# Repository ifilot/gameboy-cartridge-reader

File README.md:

# Gameboy Cartridge Reader

This project is a Gameboy cartridge reader designed around the Atmel ATmega32u4
microcontroller. It provides an easy way to interface with Gameboy cartridges,
enabling data reading, writing, and backup. The design includes a custom PCB,
firmware for the 32u4, and a simple GUI for user interaction.

> [!NOTE]
> Download a Windows 64-bit installer for the GUI [via this link](https://github.com/ifilot/gameboy-cartridge-reader/releases/latest/download/gbcr-installer-win64.exe)

## Features

* **Custom PCB**: Compact and optimized PCB designed for seamless connection with
  Gameboy cartridges and the 32u4.
* **Firmware**: Lightweight firmware written for the ATmega32u4, handling cartridge
  communication and USB interfacing.
* **GUI**: User-friendly graphical interface to manage cartridge data operations on
  your computer.
* **Open Source**: All design files, firmware, and GUI are open-source and available
  for modification.
* **Writable Cartridge Support**: Includes a [PCB design](pcb/gb-cart-sst39sf010/) 
  with an SST39SF010 chip, enabling the writing of 32KiB Gameboy games.
* **Gameboy Camera Support**: Easily extract photos taken with the 
  [Gameboy Camera](https://en.wikipedia.org/wiki/Game_Boy_Camera)
  and save them on your computer. The extracted images can be exported in a 
  variety of color palettes for a personalized look.

> [!IMPORTANT] 
> Please be aware of copyright laws regarding Gameboy and Gameboy
> Color games. Making copies of game data is strictly prohibited in many
> countries unless you own the original cartridge and are creating a backup for
> personal use where such actions are legally permitted. It is your
> responsibility to ensure compliance with local laws. This project is intended
> solely for **educational purposes** and **lawful personal** use.

## GUI

The GUI allows users to interact with their Gameboy cartridges through a
straightforward interface. Users can read ROM data from cartridges, create
backups of save files, and write new save files to supported cartridges.
Additionally, the GUI provides options for verifying data integrity, viewing
cartridge metadata (such as title and game ID), and managing writable cartridges
for flashing custom or homebrew games. Designed for simplicity, the GUI ensures
that all operations are intuitive and accessible, even for beginners.

## Bundled games

The following games are bundled with the GUI and can be readily flashed by the
user to a writeable cartridge.

* [Quartet](https://makrill.itch.io/quartet)
* [Flappybird](https://github.com/pashutk/flappybird-gameboy)

## PCB

The PCB primarily utilizes SMD components, with the exception of the 16MHz
crystal and the push button, which are through-hole components. To simplify the
soldering process, it is recommended that users order a solder paste stencil and
use a hot plate to solder the SMD components efficiently and accurately.

### Schematic

### Writeable cartridge

The writable cartridge for the Game Boy, based on the SST39SF010 flash memory
chip, offers versatile support for both TTSOP32 and PLCC32 package variants.
This flexibility allows developers and enthusiasts to choose their preferred
chip packaging without requiring additional hardware modifications. The
cartridge is designed to leverage the high-speed erase and write capabilities of
the SST39SF010, making it ideal for prototyping or homebrew games.

## Gameboy Camera Features

* Extract images directly from the Gameboy Camera cartridge.
* Customize the color scheme of the extracted photos.
* Preserve your Gameboy Camera creations in digital form.

## Firmware

The firmware for the ATmega32u4 must be compiled using Atmel Studio to ensure
compatibility and proper optimization. Once compiled, the firmware can be
flashed to the microcontroller using an ISP programmer, such as AVRDUDE, for
seamless and reliable programming.

### Fuses

See the `firmware/<DEVICE>/scripts` folder for reading and writing the fuses. 
The proper fuse settings for `lfuse`, `hfuse` and `efuse` should 
be `0xFF`, `0xD8` and `0xCB`, respectively.

## Case

A 3D-printable case for the Gameboy cartridge reader is available in the
[cases](cases) folder, providing a protective and aesthetically pleasing
enclosure for the assembled PCB.

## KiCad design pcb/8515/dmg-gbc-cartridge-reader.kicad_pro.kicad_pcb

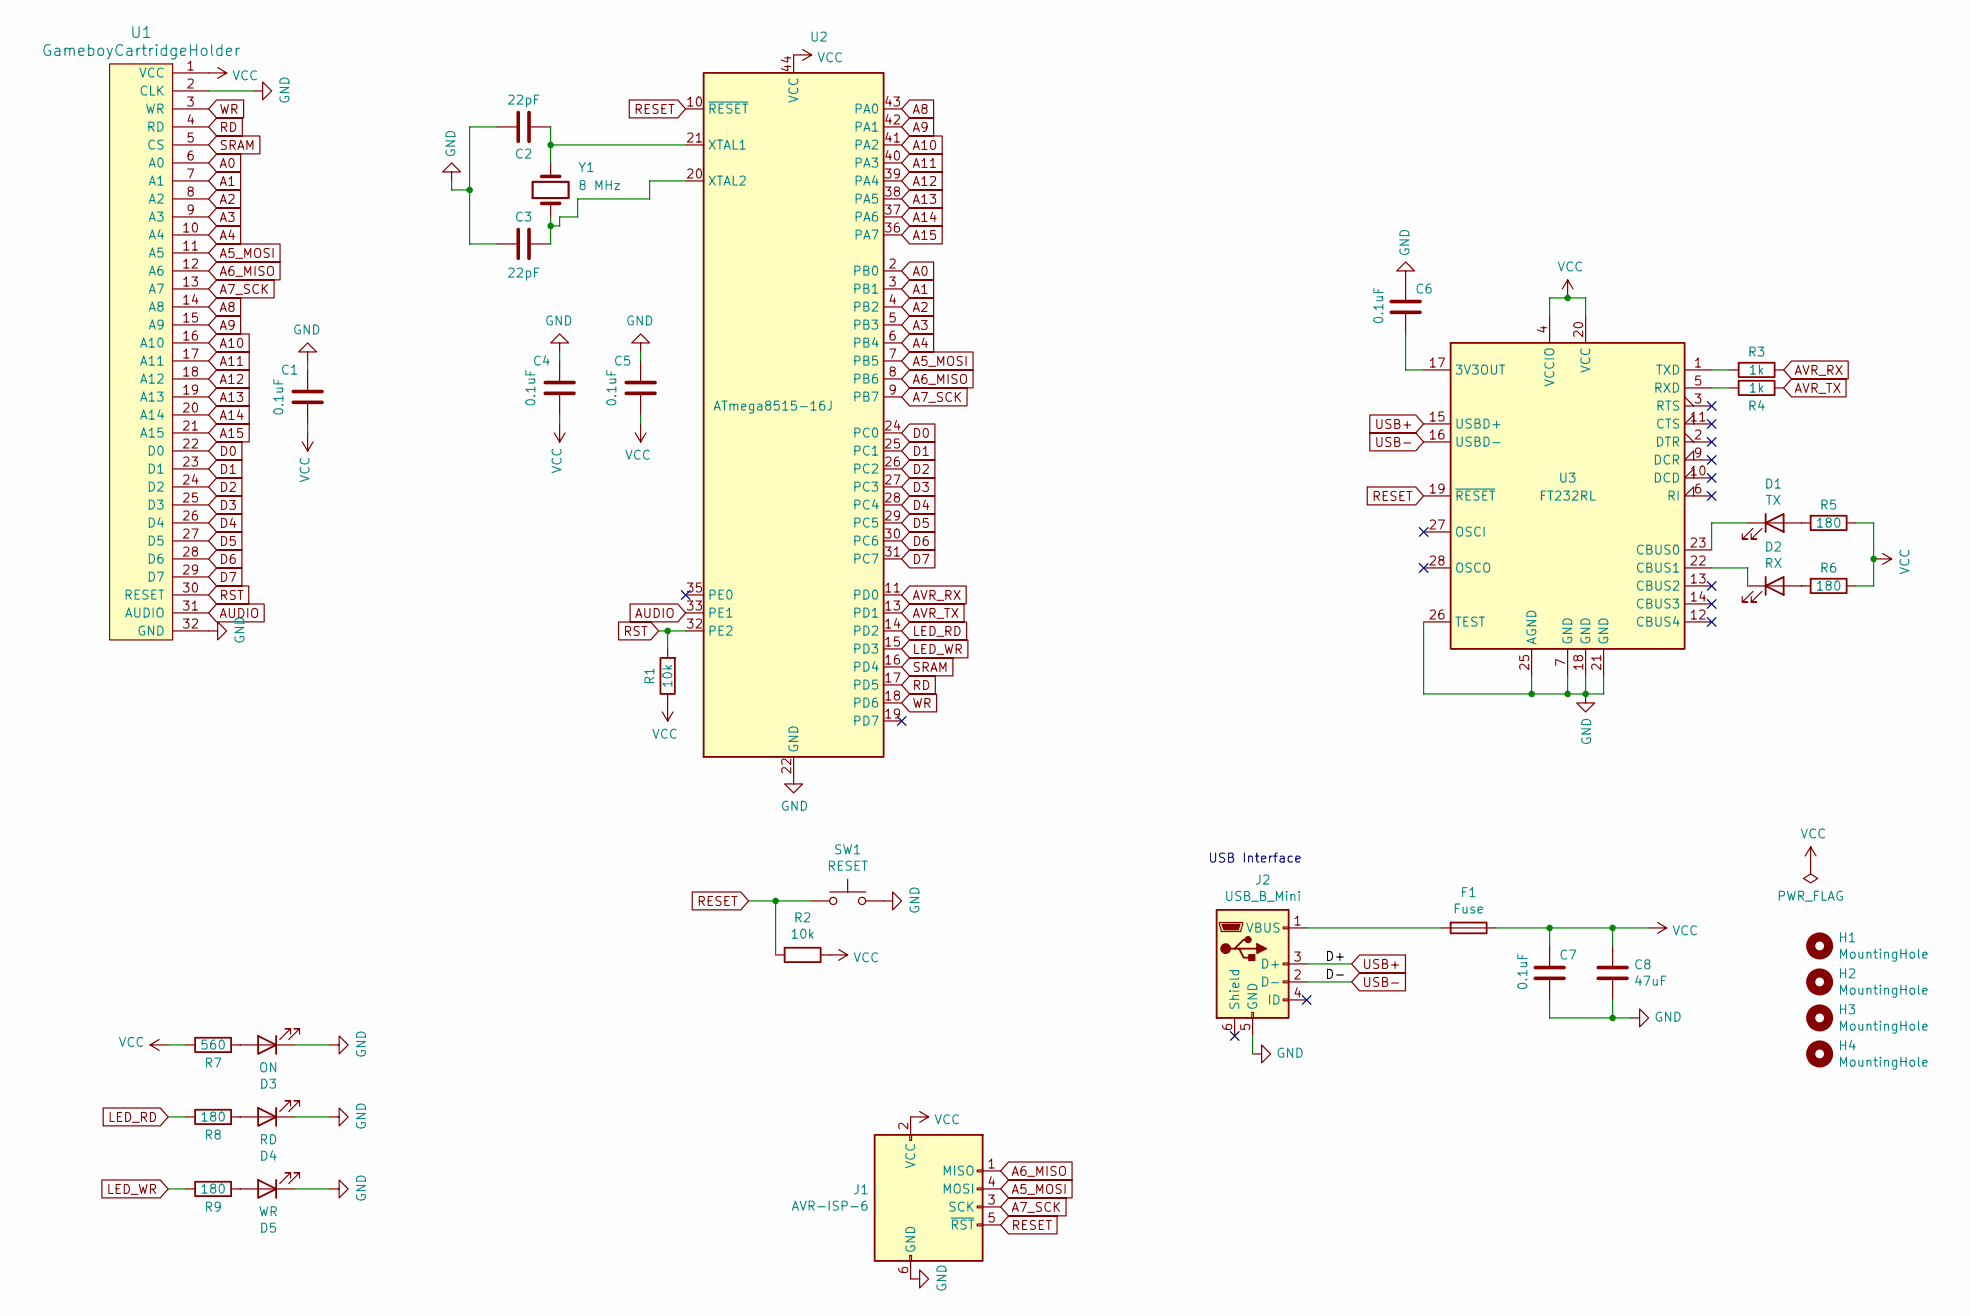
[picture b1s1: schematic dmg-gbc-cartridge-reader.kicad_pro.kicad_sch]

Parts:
C1, C4, C5, C6, C7: 0.1uF; C_0805_2012Metric_Pad1.18x1.45mm_HandSolder; LCSC C49678
C2, C3: 22pF; C_0805_2012Metric_Pad1.18x1.45mm_HandSolder; LCSC C1804
C8: 47uF; C_1206_3216Metric; LCSC C96123
D1: TX; LED_0805_2012Metric_Pad1.15x1.40mm_HandSolder; LCSC C2296
D2: RX; LED_0805_2012Metric_Pad1.15x1.40mm_HandSolder; LCSC C2296
D3: ON; LED_0805_2012Metric_Pad1.15x1.40mm_HandSolder; LCSC C2297
D4: RD; LED_0805_2012Metric_Pad1.15x1.40mm_HandSolder; LCSC C2297
D5: WR; LED_0805_2012Metric_Pad1.15x1.40mm_HandSolder; LCSC C2297
F1: Fuse; R_1206_3216Metric_Pad1.30x1.75mm_HandSolder
H1, H2, H3, H4: MountingHole; MountingHole_2.2mm_M2
J1: AVR-ISP-6; IDC-Header_2x03_P2.54mm_Vertical
J2: USB_B_Mini; 65100516121
R1, R2: 10k; R_0805_2012Metric_Pad1.20x1.40mm_HandSolder; LCSC C17902
R3, R4: 1k; R_0805_2012Metric_Pad1.20x1.40mm_HandSolder; LCSC C4410
R5, R6, R8, R9: 180; R_0805_2012Metric_Pad1.20x1.40mm_HandSolder; LCSC C4410
R7: 560; R_0805_2012Metric_Pad1.20x1.40mm_HandSolder; LCSC C4410
SW1: RESET; SW_PUSH_6mm
U1: GameboyCartridgeHolder; GBA
U2: ATmega8515-16J; PLCC-44_THT-Socket
U3: FT232RL; SSOP-28_5.3x10.2mm_P0.65mm
Y1: 8 MHz; Crystal_HC49-U_Vertical

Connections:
A0: U1.6 (A0), U2.2 (PB0)
A1: U1.7 (A1), U2.3 (PB1)
A2: U1.8 (A2), U2.4 (PB2)
A3: U1.9 (A3), U2.5 (PB3)
A4: U1.10 (A4), U2.6 (PB4)
A5_MOSI: J1.4 (MOSI), U1.11 (A5), U2.7 (PB5)
A6_MISO: J1.1 (MISO), U1.12 (A6), U2.8 (PB6)
A7_SCK: J1.3 (SCK), U1.13 (A7), U2.9 (PB7)
A8: U1.14 (A8), U2.43 (PA0)
A9: U1.15 (A9), U2.42 (PA1)
A10: U1.16 (A10), U2.41 (PA2)
A11: U1.17 (A11), U2.40 (PA3)
A12: U1.18 (A12), U2.39 (PA4)
A13: U1.19 (A13), U2.38 (PA5)
A14: U1.20 (A14), U2.37 (PA6)
A15: U1.21 (A15), U2.36 (PA7)
AUDIO: U1.31 (AUDIO), U2.33 (PE1)
AVR_RX: R3.1, U2.11 (PD0)
AVR_TX: R4.1, U2.13 (PD1)
D0: U1.22 (D0), U2.24 (PC0)
D1: U1.23 (D1), U2.25 (PC1)
D2: U1.24 (D2), U2.26 (PC2)
D3: U1.25 (D3), U2.27 (PC3)
D4: U1.26 (D4), U2.28 (PC4)
D5: U1.27 (D5), U2.29 (PC5)
D6: U1.28 (D6), U2.30 (PC6)
D7: U1.29 (D7), U2.31 (PC7)
GND: C1.1, C2.1, C3.1, C4.1, C5.1, C6.1, C7.2, C8.2, D3.1 (K), D4.1 (K), D5.1 (K), J1.6 (GND), J2.5 (GND), SW1.2, U1.2 (CLK), U1.32 (GND), U2.22 (GND), U3.7 (GND), U3.18 (GND), U3.21 (GND), U3.25 (AGND), U3.26 (TEST)
LED_RD: R8.1, U2.14 (PD2)
LED_WR: R9.1, U2.15 (PD3)
unnamed: D1.2 (A), R5.2
unnamed: D1.1 (K), U3.23 (CBUS0)
unnamed: D2.2 (A), R6.2
unnamed: D2.1 (K), U3.22 (CBUS1)
unnamed: D3.2 (A), R7.2
unnamed: D4.2 (A), R8.2
unnamed: D5.2 (A), R9.2
unnamed: F1.2, J2.1 (VBUS)
unnamed: C2.2, U2.21 (XTAL1), Y1.2
unnamed: C3.2, U2.20 (XTAL2), Y1.1
unnamed: C6.2, U3.17 (3V3OUT)
unnamed: R4.2, U3.5 (RXD)
unnamed: R3.2, U3.1 (TXD)
RD: U1.4 (RD), U2.17 (PD5)
RESET: J1.5 (~RST), R2.2, SW1.1, U2.10 (~RESET), U3.19 (~RESET)
RST: R1.2, U1.30 (RESET), U2.32 (PE2)
SRAM: U1.5 (CS), U2.16 (PD4)
USB+: J2.3 (D+), U3.15 (USBD+)
USB-: J2.2 (D-), U3.16 (USBD-)
VCC: C1.2, C4.2, C5.2, C7.1, C8.1, F1.1, J1.2 (VCC), R1.1, R2.1, R5.1, R6.1, R7.1, U1.1 (VCC), U2.44 (VCC), U3.4 (VCCIO), U3.20 (VCC)
WR: U1.3 (WR), U2.18 (PD6)

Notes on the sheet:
USB Interface

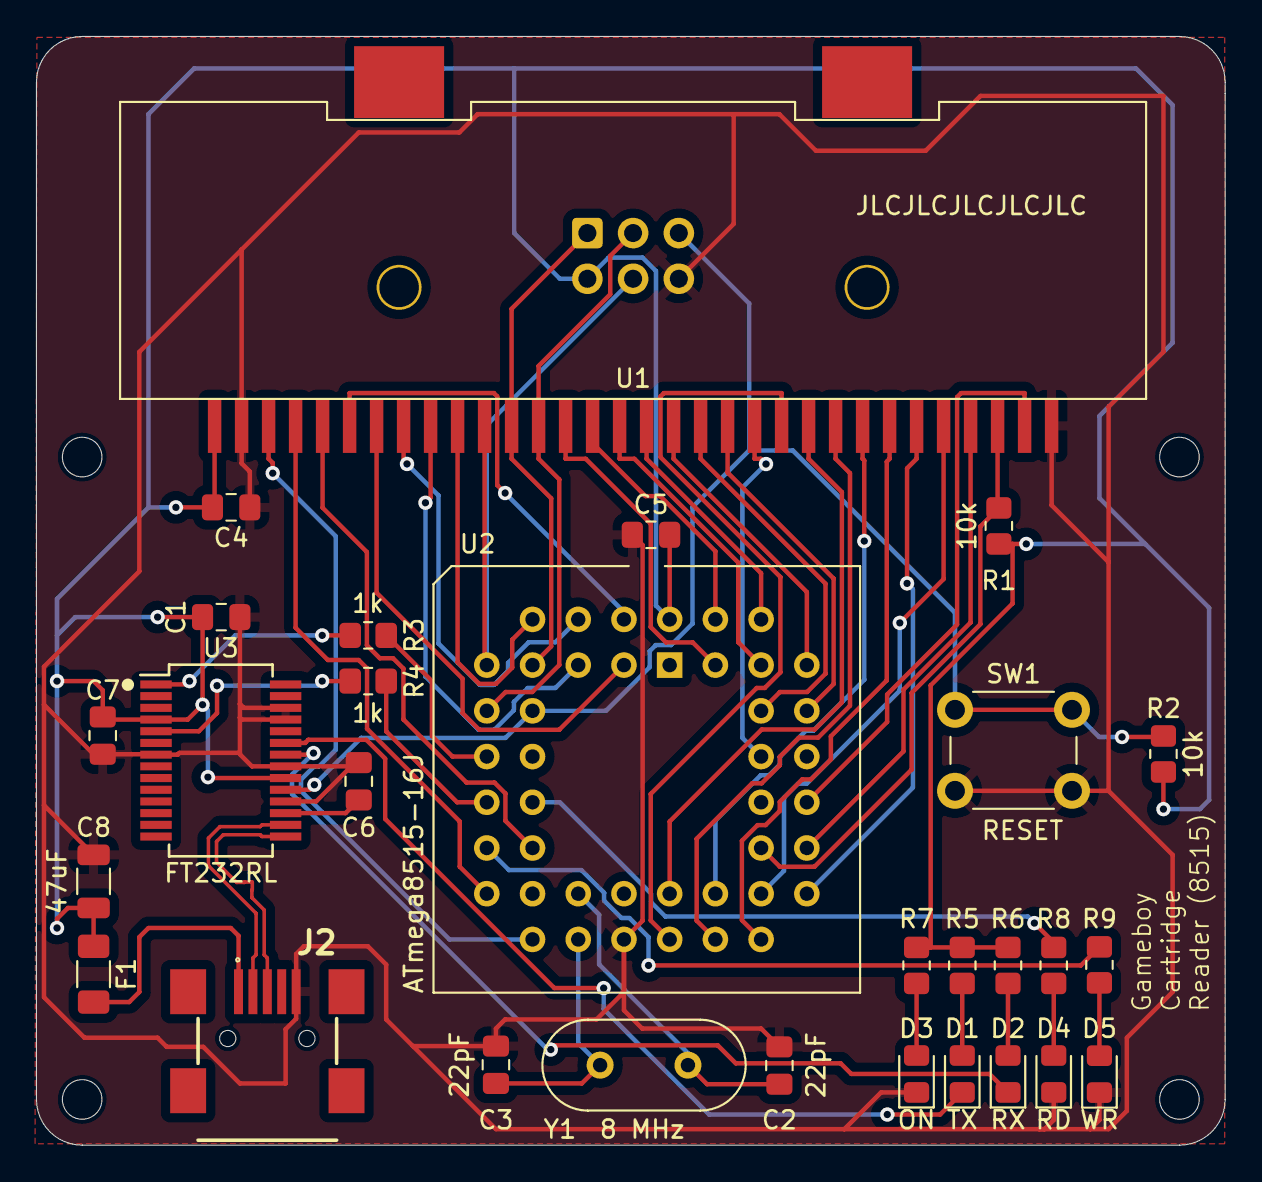
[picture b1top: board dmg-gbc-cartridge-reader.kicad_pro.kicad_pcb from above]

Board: 2 copper layers, 66.0 x 61.6 mm, 34 parts (1 on the bottom side), 51 nets.

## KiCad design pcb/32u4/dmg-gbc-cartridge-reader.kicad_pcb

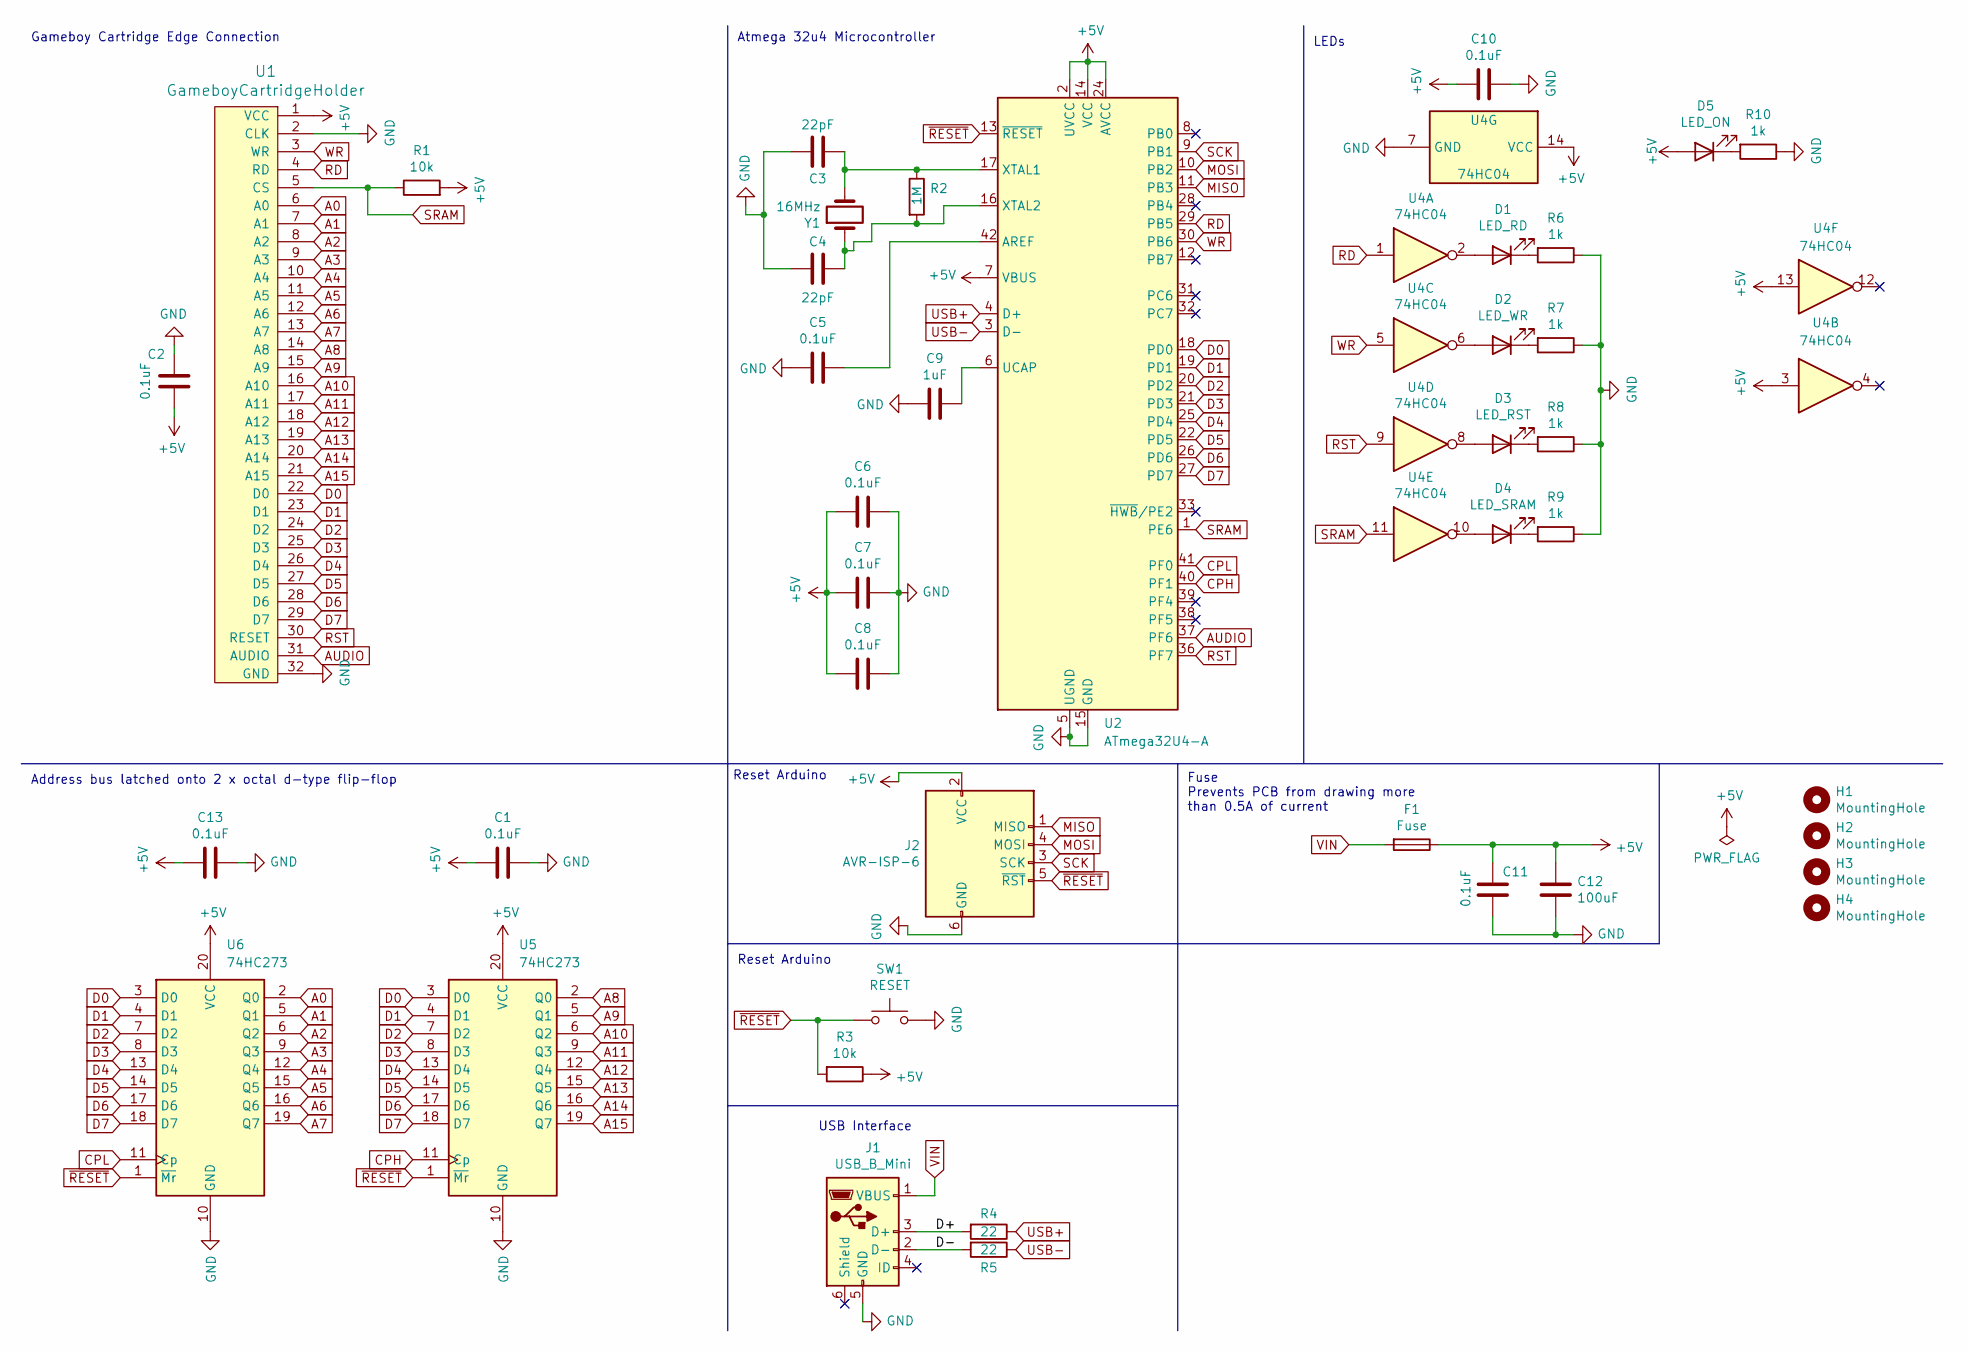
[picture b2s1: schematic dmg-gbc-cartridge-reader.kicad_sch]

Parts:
C1, C2, C5, C6, C7, C8, C10, C11, C13: 0.1uF; C_0805_2012Metric_Pad1.18x1.45mm_HandSolder; LCSC C49678
C3, C4: 22pF; C_0805_2012Metric_Pad1.18x1.45mm_HandSolder; LCSC C1804
C9: 1uF; C_0805_2012Metric_Pad1.18x1.45mm_HandSolder; LCSC C28323
C12: 100uF; C_1206_3216Metric_Pad1.33x1.80mm_HandSolder; LCSC C96123
D1: LED_RD; LED_0805_2012Metric_Pad1.15x1.40mm_HandSolder; LCSC C2296
D2: LED_WR; LED_0805_2012Metric_Pad1.15x1.40mm_HandSolder; LCSC C2296
D3: LED_RST; LED_0805_2012Metric_Pad1.15x1.40mm_HandSolder; LCSC C84256
D4: LED_SRAM; LED_0805_2012Metric_Pad1.15x1.40mm_HandSolder; LCSC C84256
D5: LED_ON; LED_0805_2012Metric_Pad1.15x1.40mm_HandSolder; LCSC C2297
F1: Fuse; R_1206_3216Metric_Pad1.30x1.75mm_HandSolder
H1, H2, H3, H4: MountingHole; MountingHole_2.2mm_M2
J1: USB_B_Mini; 65100516121
J2: AVR-ISP-6; IDC-Header_2x03_P2.54mm_Vertical
R1, R3: 10k; R_0805_2012Metric_Pad1.20x1.40mm_HandSolder; LCSC C17902
R2: 1M; R_0805_2012Metric_Pad1.20x1.40mm_HandSolder; LCSC C22935
R4, R5: 22; R_0805_2012Metric_Pad1.20x1.40mm_HandSolder; LCSC C23345
R6, R7, R8, R9, R10: 1k; R_0805_2012Metric_Pad1.20x1.40mm_HandSolder; LCSC C21190
SW1: RESET; SW_PUSH_6mm
U1: GameboyCartridgeHolder; GBA
U2: ATmega32U4-A; TQFP-44_10x10mm_P0.8mm
U4: 74HC04; SOIC-14_3.9x8.7mm_P1.27mm
U5, U6: 74HC273; SOIC-20W_7.5x12.8mm_P1.27mm
Y1: 16MHz; Crystal_HC49-U_Vertical; LCSC C13738

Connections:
+5V: C1.2, C2.2, C6.2, C7.2, C8.2, C10.2, C11.1, C12.1, C13.2, D5.2 (A), F1.1, J2.2 (VCC), R1.2, R3.1, U1.1 (VCC), U2.2 (UVCC), U2.7 (VBUS), U2.14 (VCC), U2.24 (AVCC), U2.34 (VCC), U2.44 (AVCC), U4.3, U4.13, U4.14 (VCC), U5.20 (VCC), U6.20 (VCC)
/D+: J1.3 (D+), R4.2
/D-: J1.2 (D-), R5.2
A0: U1.6 (A0), U6.2 (Q0)
A1: U1.7 (A1), U6.5 (Q1)
A2: U1.8 (A2), U6.6 (Q2)
A3: U1.9 (A3), U6.9 (Q3)
A4: U1.10 (A4), U6.12 (Q4)
A5: U1.11 (A5), U6.15 (Q5)
A6: U1.12 (A6), U6.16 (Q6)
A7: U1.13 (A7), U6.19 (Q7)
A8: U1.14 (A8), U5.2 (Q0)
A9: U1.15 (A9), U5.5 (Q1)
A10: U1.16 (A10), U5.6 (Q2)
A11: U1.17 (A11), U5.9 (Q3)
A12: U1.18 (A12), U5.12 (Q4)
A13: U1.19 (A13), U5.15 (Q5)
A14: U1.20 (A14), U5.16 (Q6)
A15: U1.21 (A15), U5.19 (Q7)
AUDIO: U1.31 (AUDIO), U2.37 (PF6)
CPH: U2.40 (PF1), U5.11 (Cp)
CPL: U2.41 (PF0), U6.11 (Cp)
D0: U1.22 (D0), U2.18 (PD0), U5.3 (D0), U6.3 (D0)
D1: U1.23 (D1), U2.19 (PD1), U5.4 (D1), U6.4 (D1)
D2: U1.24 (D2), U2.20 (PD2), U5.7 (D2), U6.7 (D2)
D3: U1.25 (D3), U2.21 (PD3), U5.8 (D3), U6.8 (D3)
D4: U1.26 (D4), U2.25 (PD4), U5.13 (D4), U6.13 (D4)
D5: U1.27 (D5), U2.22 (PD5), U5.14 (D5), U6.14 (D5)
D6: U1.28 (D6), U2.26 (PD6), U5.17 (D6), U6.17 (D6)
D7: U1.29 (D7), U2.27 (PD7), U5.18 (D7), U6.18 (D7)
GND: C1.1, C2.1, C3.1, C4.1, C5.2, C6.1, C7.1, C8.1, C9.2, C10.1, C11.2, C12.2, C13.1, J1.5 (GND), J2.6 (GND), R6.1, R7.1, R8.1, R9.1, R10.1, SW1.2, U1.2 (CLK), U1.32 (GND), U2.5 (UGND), U2.15 (GND), U2.23 (GND), U2.35 (GND), U2.43 (GND), U4.7 (GND), U5.10 (GND), U6.10 (GND)
MISO: J2.1 (MISO), U2.11 (PB3)
MOSI: J2.4 (MOSI), U2.10 (PB2)
unnamed: D1.2 (A), U4.2
unnamed: D1.1 (K), R6.2
unnamed: D2.2 (A), U4.6
unnamed: D2.1 (K), R7.2
unnamed: D3.2 (A), U4.8
unnamed: D3.1 (K), R8.2
unnamed: D4.2 (A), U4.10
unnamed: D4.1 (K), R9.2
unnamed: D5.1 (K), R10.2
unnamed: C5.1, U2.42 (AREF)
unnamed: C9.1, U2.6 (UCAP)
unnamed: C3.2, R2.1, U2.17 (XTAL1), Y1.2
unnamed: C4.2, R2.2, U2.16 (XTAL2), Y1.1
RD: U1.4 (RD), U2.29 (PB5), U4.1
RST: U1.30 (RESET), U2.36 (PF7), U4.9
SCK: J2.3 (SCK), U2.9 (PB1)
SRAM: R1.1, U1.5 (CS), U2.1 (PE6), U4.11
USB+: R4.1, U2.4 (D+)
USB-: R5.1, U2.3 (D-)
VIN: F1.2, J1.1 (VBUS)
WR: U1.3 (WR), U2.30 (PB6), U4.5
~RESET: J2.5 (~RST), R3.2, SW1.1, U2.13 (~RESET), U5.1 (~Mr), U6.1 (~Mr)

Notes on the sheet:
Address bus latched onto 2 x octal d-type flip-flop
Reset Arduino
Atmega 32u4 Microcontroller
LEDs
Gameboy Cartridge Edge Connection
USB Interface
Fuse Prevents PCB from drawing more than 0.5A of current

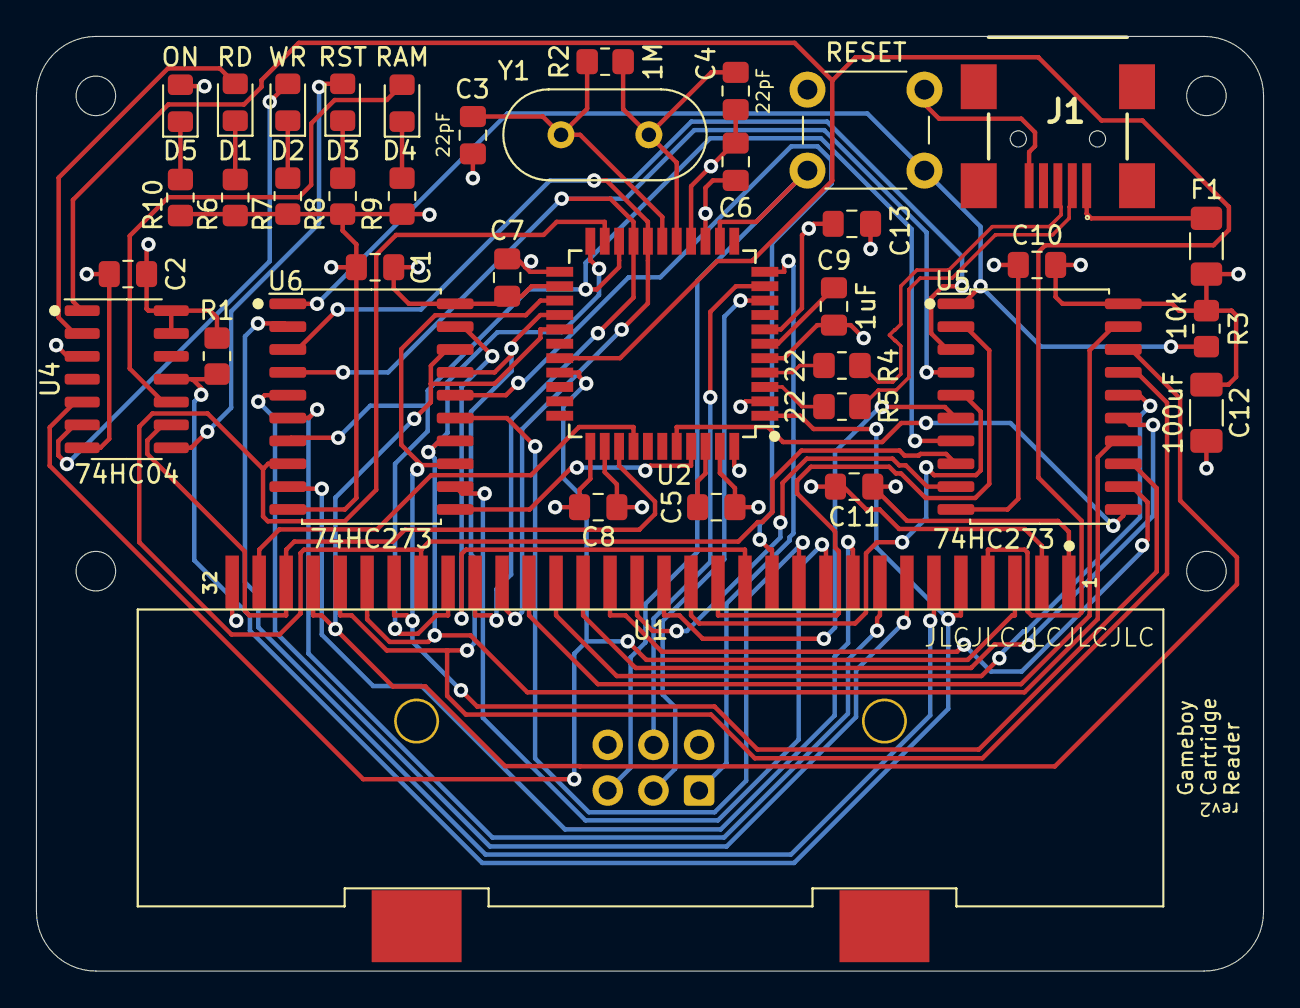
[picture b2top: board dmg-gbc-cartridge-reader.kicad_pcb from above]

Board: 4 copper layers, 68.2 x 51.9 mm, 42 parts (1 on the bottom side), 55 nets.

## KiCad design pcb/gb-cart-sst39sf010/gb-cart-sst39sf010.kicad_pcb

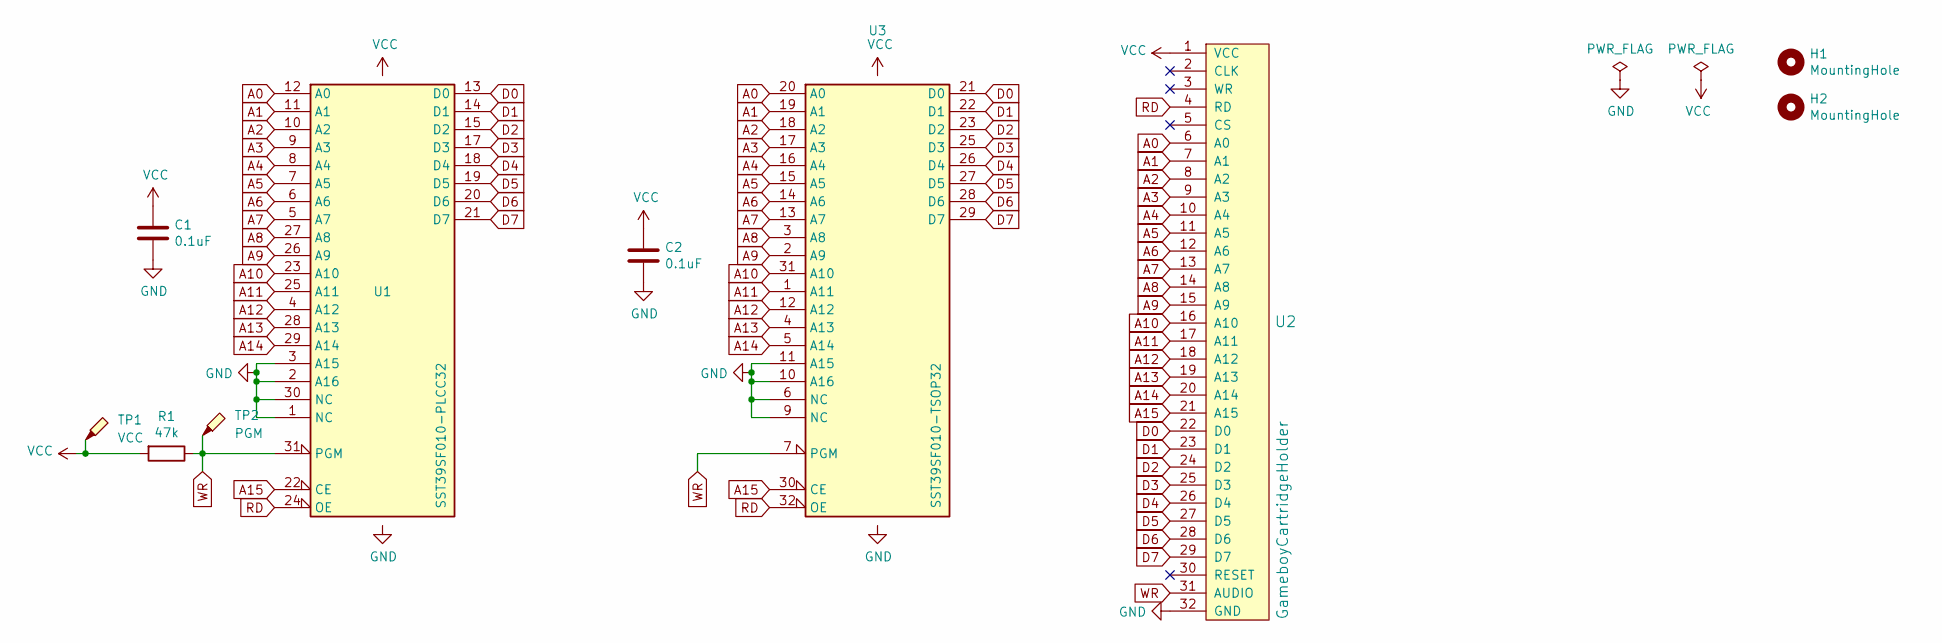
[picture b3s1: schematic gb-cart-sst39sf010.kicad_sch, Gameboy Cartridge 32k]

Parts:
C1, C2: 0.1uF; C_0805_2012Metric_Pad1.18x1.45mm_HandSolder
H1: MountingHole; MountingHole_7.2mm
H2: MountingHole; MountingHole_2.3mm
R1: 47k; R_0805_2012Metric_Pad1.20x1.40mm_HandSolder
TP1: VCC; TestPoint_Pad_D1.5mm
TP2: PGM; TestPoint_Pad_D1.5mm
U1: SST39SF010-PLCC32; PLCC-32_11.4x14.0mm_P1.27mm
U2: GameboyCartridgeHolder; GameBoy_Cartridge_1x32_P1.50mm_Edge
U3: SST39SF010-TSOP32; TSOP-I-32_11.8x8mm_P0.5mm

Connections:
A0: U1.12 (A0), U2.6 (A0), U3.20 (A0)
A1: U1.11 (A1), U2.7 (A1), U3.19 (A1)
A2: U1.10 (A2), U2.8 (A2), U3.18 (A2)
A3: U1.9 (A3), U2.9 (A3), U3.17 (A3)
A4: U1.8 (A4), U2.10 (A4), U3.16 (A4)
A5: U1.7 (A5), U2.11 (A5), U3.15 (A5)
A6: U1.6 (A6), U2.12 (A6), U3.14 (A6)
A7: U1.5 (A7), U2.13 (A7), U3.13 (A7)
A8: U1.27 (A8), U2.14 (A8), U3.3 (A8)
A9: U1.26 (A9), U2.15 (A9), U3.2 (A9)
A10: U1.23 (A10), U2.16 (A10), U3.31 (A10)
A11: U1.25 (A11), U2.17 (A11), U3.1 (A11)
A12: U1.4 (A12), U2.18 (A12), U3.12 (A12)
A13: U1.28 (A13), U2.19 (A13), U3.4 (A13)
A14: U1.29 (A14), U2.20 (A14), U3.5 (A14)
A15: U1.22 (CE), U2.21 (A15), U3.30 (CE)
D0: U1.13 (D0), U2.22 (D0), U3.21 (D0)
D1: U1.14 (D1), U2.23 (D1), U3.22 (D1)
D2: U1.15 (D2), U2.24 (D2), U3.23 (D2)
D3: U1.17 (D3), U2.25 (D3), U3.25 (D3)
D4: U1.18 (D4), U2.26 (D4), U3.26 (D4)
D5: U1.19 (D5), U2.27 (D5), U3.27 (D5)
D6: U1.20 (D6), U2.28 (D6), U3.28 (D6)
D7: U1.21 (D7), U2.29 (D7), U3.29 (D7)
GND: C1.2, C2.2, U1.1 (NC), U1.2 (A16), U1.3 (A15), U1.16 (GND), U1.30 (NC), U2.32 (GND), U3.6 (NC), U3.9 (NC), U3.10 (A16), U3.11 (A15), U3.24 (GND)
RD: U1.24 (OE), U2.4 (RD), U3.32 (OE)
VCC: C1.1, C2.1, R1.2, TP1.1, U1.32 (VCC), U2.1 (VCC), U3.8 (VCC)
WR: R1.1, TP2.1, U1.31 (PGM), U2.31 (AUDIO), U3.7 (PGM)

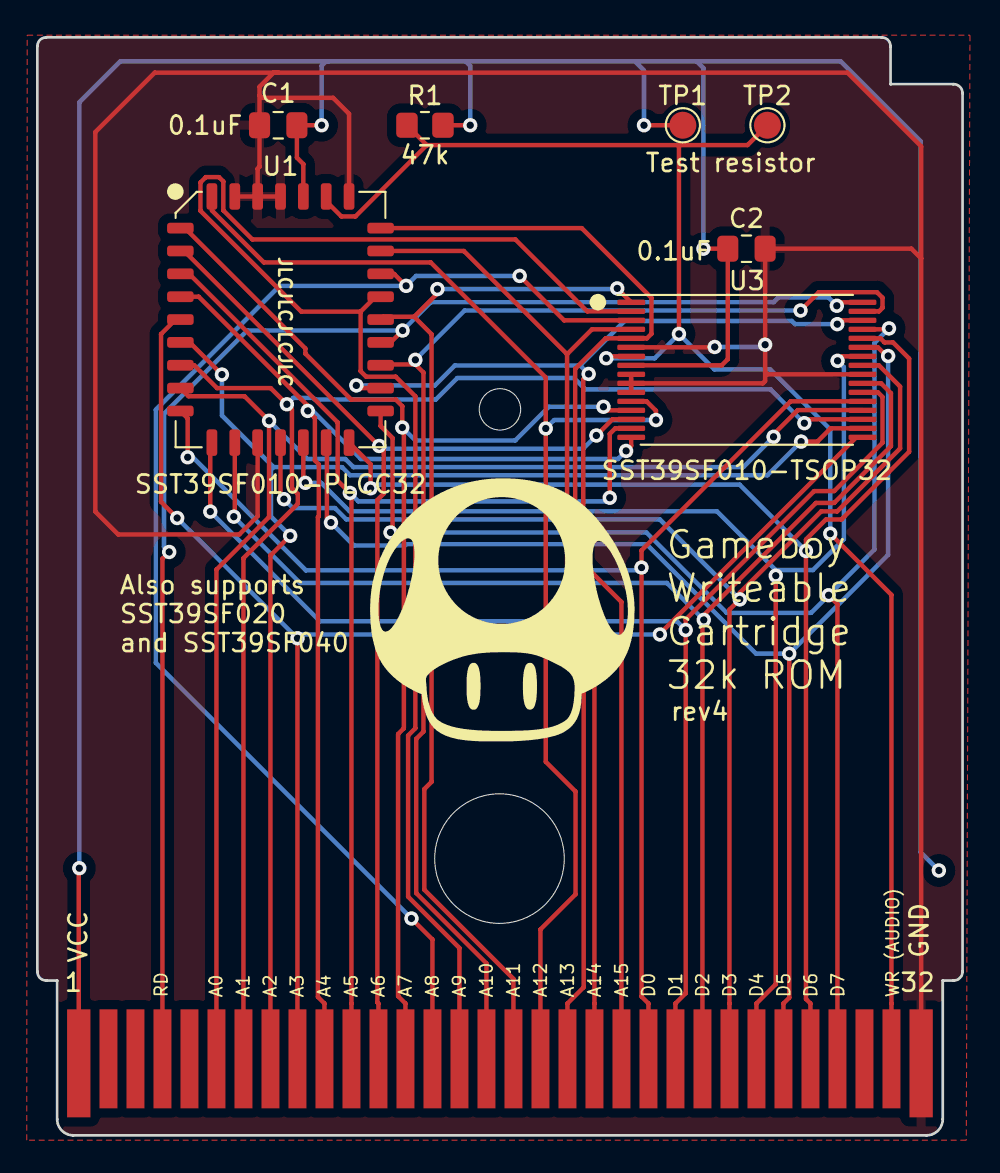
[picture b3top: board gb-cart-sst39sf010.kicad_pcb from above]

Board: 2 copper layers, 51.4 x 61.0 mm, 11 parts (0 on the bottom side), 28 nets.

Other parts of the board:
G0001: LOGO; mushroom

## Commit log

2025-01-14 Removing incompatible designs
2025-01-14 Expanding README.md
2025-01-14 Removing Dropbox deployment
2025-01-14 Updating README.md
2025-01-14 Updating image
2025-01-14 Adding images
2025-01-14 Removing background from images
2025-01-14 Reduce size
2025-01-14 Adding information for Gameboy Camera

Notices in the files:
README.md:
License: GPL v3
License: CC BY-SA 4.0
